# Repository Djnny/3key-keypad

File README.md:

# Overview
3key keypad for ring+index players

This document will act as a sort of design goals/challenges log until the project is complete.

# Design Goals
The main objective for this project is to design and build a working keypad that accomodates the ring+index playstyle in osu, as well as provide me with experience to shift to larger projects in the future.

Some of the features I would like to have in the final project include:
- practical pcb with kailh hotswap socket support
- working rgb underglow leds
- custom QMK firmware
- extra buttons for miscellaneous ingame functions
- OLED display support because why not
- stylish looking case

# Guides/Resources Used
- https://wiki.ai03.com/books/pcb-design/page/pcb-guide-part-1---preparations
- https://www.masterzen.fr/2020/05/03/designing-a-keyboard-part-1/
- https://www.arduino.cc/en/uploads/Main/arduino-micro-schematic.pdf
- https://docs.google.com/document/d/1xsjb1sf3pxFw8bXC4gNhWsFhWNOthMoyz6RiJc1UtVI/edit
- http://ww1.microchip.com/downloads/en/devicedoc/atmel-7766-8-bit-avr-atmega16u4-32u4_datasheet.pdf

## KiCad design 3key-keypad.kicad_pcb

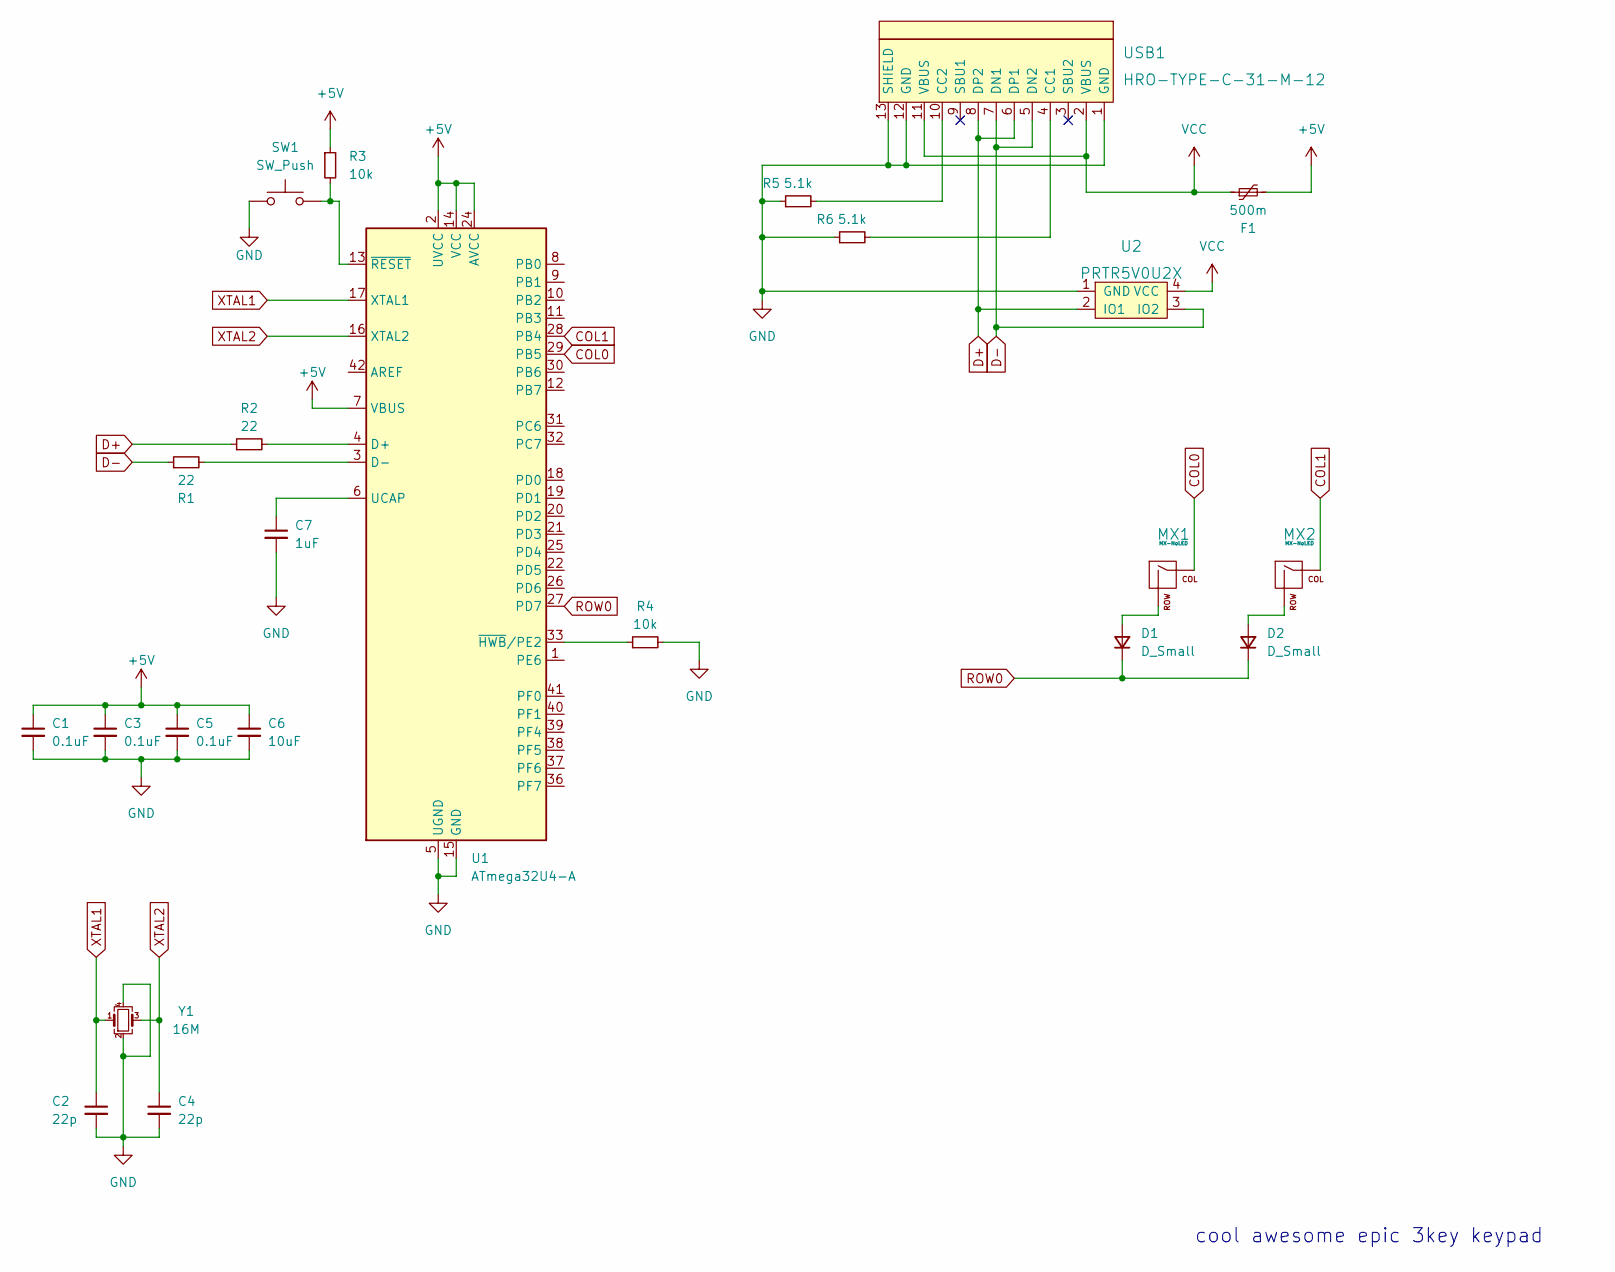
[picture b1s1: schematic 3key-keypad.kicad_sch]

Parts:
C1, C3, C5: 0.1uF; C_0805_2012Metric
C2, C4: 22p; C_0805_2012Metric
C6: 10uF; C_0805_2012Metric
C7: 1uF; C_0805_2012Metric
D1, D2: D_Small; D_SOD-123
F1: 500m; Fuse_1206_3216Metric
MX1, MX2: MX-NoLED; MX-1U-NoLED
R1, R2: 22; R_0805_2012Metric
R3, R4: 10k; R_0805_2012Metric
R5, R6: 5.1k; R_0805_2012Metric
SW1: SW_Push; SKQG-1155865
U1: ATmega32U4-A; TQFP-44_10x10mm_P0.8mm
U2: PRTR5V0U2X; SOT143B
USB1: HRO-TYPE-C-31-M-12; HRO-TYPE-C-31-M-12-HandSoldering
Y1: 16M; Crystal_SMD_3225-4Pin_3.2x2.5mm

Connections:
+5V: C1.1, C3.1, C5.1, C6.1, F1.2, R3.1, U1.2 (UVCC), U1.7 (VBUS), U1.14 (VCC), U1.24 (AVCC), U1.34 (VCC), U1.44 (AVCC)
COL0: MX1.1 (COL), U1.29 (PB5)
COL1: MX2.1 (COL), U1.28 (PB4)
D+: R2.1, U2.2 (IO1), USB1.6 (DP1), USB1.8 (DP2)
D-: R1.1, U2.3 (IO2), USB1.5 (DN2), USB1.7 (DN1)
GND: C1.2, C2.2, C3.2, C4.2, C5.2, C6.2, C7.2, R4.2, R5.1, R6.1, SW1.1, U1.5 (UGND), U1.15 (GND), U1.23 (GND), U1.35 (GND), U1.43 (GND), U2.1 (GND), USB1.1 (GND), USB1.12 (GND), USB1.13 (SHIELD), Y1.2, Y1.4
unnamed: C7.1, U1.6 (UCAP)
unnamed: D1.2 (A), MX1.2 (ROW)
unnamed: D2.2 (A), MX2.2 (ROW)
unnamed: R1.2, U1.3 (D-)
unnamed: R2.2, U1.4 (D+)
unnamed: R3.2, SW1.2, U1.13 (~RESET)
unnamed: R4.1, U1.33 (~HWB/PE2)
unnamed: R5.2, USB1.10 (CC2)
unnamed: R6.2, USB1.4 (CC1)
ROW0: D1.1 (K), D2.1 (K), U1.27 (PD7)
VCC: F1.1, U2.4 (VCC), USB1.2 (VBUS), USB1.11 (VBUS)
XTAL1: C2.1, U1.17 (XTAL1), Y1.1
XTAL2: C4.1, U1.16 (XTAL2), Y1.3

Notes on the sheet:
cool awesome epic 3key keypad

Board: 2 copper layers, 23 parts (0 on the bottom side), 19 nets, no tracks yet.

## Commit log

2022-06-10 initialized kicad project
2022-06-10 placed basic components on schematic,
    fixed repository business, added libraries
2022-06-10 created .gitignore
2022-06-10 added resources to readme
2022-06-11 added 2key matrix to schematic
2022-06-11 assigned footprints and made basic layout
